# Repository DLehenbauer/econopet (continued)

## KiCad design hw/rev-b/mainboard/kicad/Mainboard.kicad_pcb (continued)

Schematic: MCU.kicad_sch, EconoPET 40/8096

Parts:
C3, C6, C90, C93, C94, C95, C96, C97, C98: 100n; C_0402_1005Metric; LCSC Part # C307331
C86, C87: 33p; C_0402_1005Metric; LCSC Part # C1562
C88, C91, C92: 2u2 6.3V; C_0402_1005Metric; LCSC Part # C12530
D11: LED_GRN; LED_0603_1608Metric; LCSC Part # C2986059
J23: MENU; PinHeader_1x02_P2.54mm_Vertical; MOUSER 649-1012937891002BLF
JP7: DVI_CEC; SolderJumper-2_P1.3mm_Open_RoundedPad1.0x1.5mm
R39: 10k; R_0402_1005Metric; LCSC Part # C25744
R40: 4k7; R_0402_1005Metric; LCSC Part # C25900
R41, R42, R43: 1k; R_0402_1005Metric; LCSC Part # C11702
R44, R45, R48, R49: 2k2; R_0402_1005Metric; LCSC Part # C25879
R46, R47: 27; R_0603_1608Metric; LCSC Part # C25190
SW4: TS-1088-AR02016; SW-SMD_L3.9-W3.0-P4.45; LCSC Part # C720477
SW5: MENU_BTN; APEM_MJTP1117; MOUSER 642-MJTP1117
U21: RP2040; LQFN-56_L7.0-W7.0-P0.4-EP; LCSC Part # C2040
Y1: 12 MHz; Crystal_SMD_3225-4Pin_3.2x2.5mm; LCSC Part # C9002

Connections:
+3V3: C92.1, C93.1, C94.1, C95.1, C96.1, C97.1, C98.1, R40.1, R44.1, R45.1, R48.1, R49.1, U21.1 (IOVDD), U21.10 (IOVDD), U21.22 (IOVDD), U21.33 (IOVDD), U21.42 (IOVDD), U21.43 (ADC_AVDD), U21.44 (VREG_IN), U21.48 (USB_VDD), U21.49 (IOVDD); also elsewhere on the board
/MAGIC/FPGA/CEC: JP7.1 (A), U21.36 (GPIO24); also elsewhere on the board
/MAGIC/FPGA/FPGA_CLK: U21.18 (GPIO15); also elsewhere on the board
/MAGIC/FPGA/I2C0_SCL: R49.2, U21.41 (GPIO29_ADC3); also elsewhere on the board
/MAGIC/FPGA/I2C0_SDA: R48.2, U21.40 (GPIO28_ADC2); also elsewhere on the board
/MAGIC/FPGA/I2C1_SCL: R45.2, U21.5 (GPIO3); also elsewhere on the board
/MAGIC/FPGA/I2C1_SDA: R44.2, U21.4 (GPIO2); also elsewhere on the board
/MAGIC/FPGA/SPI0_RX: U21.6 (GPIO4); also elsewhere on the board
/MAGIC/FPGA/SPI0_SCK: U21.8 (GPIO6); also elsewhere on the board
/MAGIC/FPGA/SPI0_TX: U21.9 (GPIO7); also elsewhere on the board
/MAGIC/FPGA/SPI0_~CS: U21.7 (GPIO5); also elsewhere on the board
/MAGIC/FPGA/SPI1_RX: U21.15 (GPIO12); also elsewhere on the board
/MAGIC/FPGA/SPI1_SCK: U21.17 (GPIO14); also elsewhere on the board
/MAGIC/FPGA/SPI1_TX: U21.14 (GPIO11); also elsewhere on the board
/MAGIC/FPGA/SPI1_~CS: U21.16 (GPIO13); also elsewhere on the board
/MAGIC/FPGA/SPI1_~READY: U21.13 (GPIO10); also elsewhere on the board
/MAGIC/FPGA/SWCLK: U21.24 (SWCLK); also elsewhere on the board
/MAGIC/FPGA/SWD: U21.25 (SWD); also elsewhere on the board
/MAGIC/FPGA/UART_RX: U21.3 (GPIO1); also elsewhere on the board
/MAGIC/FPGA/UART_TX: U21.2 (GPIO0); also elsewhere on the board
/MAGIC/FPGA/~CRESET: R39.2; also elsewhere on the board
/MAGIC/FPGA/~SPI_ENA: C6.1, R40.2, R41.2, U21.26 (RUN); also elsewhere on the board
/MAGIC/MCU/DVDD: C3.1, C90.1, C91.1, U21.23 (DVDD), U21.45 (VREG_VOUT), U21.50 (DVDD)
/MAGIC/MCU/DVI/CEC: JP7.2 (B); also elsewhere on the board
/MAGIC/MCU/DVI/DVI_CK+: U21.28 (GPIO17); also elsewhere on the board
/MAGIC/MCU/DVI/DVI_CK-: U21.27 (GPIO16); also elsewhere on the board
/MAGIC/MCU/DVI/DVI_D0+: U21.30 (GPIO19); also elsewhere on the board
/MAGIC/MCU/DVI/DVI_D0-: U21.29 (GPIO18); also elsewhere on the board
/MAGIC/MCU/DVI/DVI_D1+: U21.32 (GPIO21); also elsewhere on the board
/MAGIC/MCU/DVI/DVI_D1-: U21.31 (GPIO20); also elsewhere on the board
/MAGIC/MCU/DVI/DVI_D2+: U21.35 (GPIO23); also elsewhere on the board
/MAGIC/MCU/DVI/DVI_D2-: U21.34 (GPIO22); also elsewhere on the board
/MAGIC/MCU/Flash/SCK: U21.52 (QSPI_SCLK); also elsewhere on the board
/MAGIC/MCU/Flash/SD0: U21.53 (QSPI_SD0); also elsewhere on the board
/MAGIC/MCU/Flash/SD1: U21.55 (QSPI_SD1); also elsewhere on the board
/MAGIC/MCU/Flash/SD2: U21.54 (QSPI_SD2); also elsewhere on the board
/MAGIC/MCU/Flash/SD3: U21.51 (QSPI_SD3); also elsewhere on the board
/MAGIC/MCU/Flash/~CS: U21.56 (QSPI_SS); also elsewhere on the board
/MAGIC/MCU/GP25: R43.1, U21.37 (GPIO25)
/MAGIC/MCU/GP27: C88.1, J23.2, SW5.2, U21.39 (GPIO27_ADC1)
/MAGIC/MCU/MCU_USB_D+: R46.1, U21.47 (USB_DP)
/MAGIC/MCU/MCU_USB_D-: R47.1, U21.46 (USB_DM)
/MAGIC/MCU/MCU_~CRESET: R39.1, U21.38 (GPIO26_ADC0)
/MAGIC/MCU/SD_DETECT: U21.11 (GPIO8); also elsewhere on the board
/MAGIC/MCU/SD_~CS: U21.12 (GPIO9); also elsewhere on the board
/MAGIC/MCU/USB/USB_D+: R46.2; also elsewhere on the board
/MAGIC/MCU/USB/USB_D-: R47.2; also elsewhere on the board
/MAGIC/MCU/XIN: C86.2, U21.20 (XIN), Y1.1
/MAGIC/MCU/XOUT: R42.2, U21.21 (XOUT)
GND: C3.2, C6.2, C86.1, C87.1, C88.2, C90.2, C91.2, C92.2, C93.2, C94.2, C95.2, C96.2, C97.2, C98.2, D11.1 (K), J23.1, SW4.1, SW5.1, U21.19 (TESTEN), U21.57 (GND), Y1.2, Y1.4; also elsewhere on the board
unnamed: C87.2, R42.1, Y1.3
unnamed: D11.2 (A), R43.2
unnamed: R41.1, SW4.2

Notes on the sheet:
100n at RUN pin for EMI immunity. Avoids reset during CRT sync lock.
IO/USB/AVDD Decoupling
The MCU configures the FPGA using SPI0. Once the FPGA is configured, the MCU can communicate asynchronously with the system bus over SPI0 using the FPGA as a bridge. The MCU uses SPI0 to initialize SRAM with the PET ROM contents at POR. Afterwards, Core0 of the MCU uses SPI0 to read back video RAM 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
Menu/Reset Button
Oscillator Specs: C_{L}=20pF C_{0}=7pF DL=1-200μW (100uW typical) ESR=80Ω Load capacitor calculation: C = 2*C_{L} - 2*C_{stray} C_{L} = 20pf, C_{stray} = 2-5pF C = 30-36pF AMS1117-3.3 may require increasing PICO_XOSC_STARTUP_DELAY_MULTIPLIER to allow more time for 3V3 to stabilize. The TLV1117LV ap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
The T8/20Q144 requires SPI0_~{CS} to be pulsed low, even when using JTAG. To prevent contention on SPI0_~{CS}, we use ~{SPI_ENA} to reset the RP2040, which then detects that ~{CRESET} is being actively driven hi and skips JTAG configuration. POR Idle Programming ~SPI0_~{CS} float hi Pulse lo -> hi 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
MCU
MCU Status LED
On short press, MCU triggers a CPU reset. On long press, MCU enters menu.
DVDD Decoupling
10k resistor allows FPGA programmer to override ~{CRESET} during JTAG configuration.

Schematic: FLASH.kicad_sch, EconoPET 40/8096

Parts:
C1: 100n; C_0402_1005Metric; LCSC Part # C307331
R65: 1k; R_0402_1005Metric; LCSC Part # C11702
R66: 10k; R_0402_1005Metric; LCSC Part # C25744
SW6: TS-1088-AR02016; SW-SMD_L3.9-W3.0-P4.45; LCSC Part # C720477
U22: W25Q128JVS; SOIC-8_5.23x5.23mm_P1.27mm; LCSC Part # C97521

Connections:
+3V3: C1.1, R66.1, U22.8 (VCC); also elsewhere on the board
/MAGIC/MCU/Flash/SCK: U22.6 (CLK); also elsewhere on the board
/MAGIC/MCU/Flash/SD0: U22.5 (DI(IO0)); also elsewhere on the board
/MAGIC/MCU/Flash/SD1: U22.2 (DO(IO1)); also elsewhere on the board
/MAGIC/MCU/Flash/SD2: U22.3 (IO2); also elsewhere on the board
/MAGIC/MCU/Flash/SD3: U22.7 (IO3); also elsewhere on the board
/MAGIC/MCU/Flash/~CS: R65.2, R66.2, U22.1 (~CS); also elsewhere on the board
GND: C1.2, SW6.1, U22.4 (GND); also elsewhere on the board
unnamed: R65.1, SW6.2

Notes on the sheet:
16MiB Quad SPI flash memory for MCU. Holding BOOTSEL at power on puts the MCU into programming mode, allowing new firmware to be uploaded via USB for initial programming and recovery. (Typically, firmware updates happen via microSD instead.)
Flash

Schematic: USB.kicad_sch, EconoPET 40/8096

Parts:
C102: 47u 10V; C_1206_3216Metric; LCSC Part # C96123
C103: 1u; C_0402_1005Metric; LCSC Part # C52923
D12: SS54; D_SMA; LCSC Part # C22452
J26: USB1.1_HOST_TYPE_C; USB-C_SMD-TYPE-C-31-M-12; LCSC Part # C165948
R63, R64: 56k; R_0402_1005Metric; LCSC Part # C25796

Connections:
+5V: D12.2 (A); also elsewhere on the board
/MAGIC/MCU/USB/CC1: J26.A5 (CC1), R63.2
/MAGIC/MCU/USB/CC2: J26.B5 (CC2), R64.2
/MAGIC/MCU/USB/USB_D+: J26.A6 (D+), J26.B6 (D+); also elsewhere on the board
/MAGIC/MCU/USB/USB_D-: J26.A7 (D-), J26.B7 (D-); also elsewhere on the board
/MAGIC/MCU/USB/VBUS: C102.1, C103.1, D12.1 (K), J26.A4_B9 (VBUS), J26.A9_B4 (VBUS), R63.1, R64.1
GND: C102.2, C103.2, J26.A1_B12 (GND), J26.A12_B1 (GND), J26.S1 (SHIELD); also elsewhere on the board

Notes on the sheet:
USB
USB 1.1 Host over USB-C connector The 56k pullups on CC1 and CC2 identify the port as downstream facing, supplying 5V/900ma. The diode prevents connected devices from inadvertently backpowering the EconoPET. V_{F} < 0.5V should be within USB spec of 5V +/-10% (4.5V - 5.5V). The 47u capacitor helps 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

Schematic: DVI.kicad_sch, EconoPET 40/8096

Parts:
C99: 4u7 10V; C_0402_1005Metric; LCSC Part # C23733
J24: NOT_HDMI_A; HDMI_A_Molex_208658-1001_Horizontal; LCSC Part # C138388
R50, R51, R52: 2k2; R_0402_1005Metric; LCSC Part # C25879
R53, R54, R55, R56, R57, R58, R59, R60, R61: 270; R_0603_1608Metric; LCSC Part # C22966

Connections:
+3V3: R50.1; also elsewhere on the board
+5V: C99.1, J24.18 (+5V), R51.1, R52.1; also elsewhere on the board
/MAGIC/MCU/DVI/CEC: R50.2, R61.1; also elsewhere on the board
/MAGIC/MCU/DVI/DVI_CK+: R59.1; also elsewhere on the board
/MAGIC/MCU/DVI/DVI_CK-: R60.1; also elsewhere on the board
/MAGIC/MCU/DVI/DVI_D0+: R57.1; also elsewhere on the board
/MAGIC/MCU/DVI/DVI_D0-: R58.1; also elsewhere on the board
/MAGIC/MCU/DVI/DVI_D1+: R55.1; also elsewhere on the board
/MAGIC/MCU/DVI/DVI_D1-: R56.1; also elsewhere on the board
/MAGIC/MCU/DVI/DVI_D2+: R53.1; also elsewhere on the board
/MAGIC/MCU/DVI/DVI_D2-: R54.1; also elsewhere on the board
/MAGIC/MCU/DVI/HDMI_CEC: J24.13 (CEC), R61.2
/MAGIC/MCU/DVI/HDMI_CK+: J24.10 (CK+), R59.2
/MAGIC/MCU/DVI/HDMI_CK-: J24.12 (CK-), R60.2
/MAGIC/MCU/DVI/HDMI_D0+: J24.7 (D0+), R57.2
/MAGIC/MCU/DVI/HDMI_D0-: J24.9 (D0-), R58.2
/MAGIC/MCU/DVI/HDMI_D1+: J24.4 (D1+), R55.2
/MAGIC/MCU/DVI/HDMI_D1-: J24.6 (D1-), R56.2
/MAGIC/MCU/DVI/HDMI_D2+: J24.1 (D2+), R53.2
/MAGIC/MCU/DVI/HDMI_D2-: J24.3 (D2-), R54.2
GND: C99.2, J24.2 (D2S), J24.5 (D1S), J24.8 (D0S), J24.11 (CKS), J24.17 (GND), J24.SH; also elsewhere on the board
unnamed: J24.15 (SCL), R51.2
unnamed: J24.16 (SDA), R52.2

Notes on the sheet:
NOT
DVI TMDS protocol over an HDMI-compatible connector (not HDMI certified). See: https://github.com/Wren6991/PicoDVI
DVI VIDEO

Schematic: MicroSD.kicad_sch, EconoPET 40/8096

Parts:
C2: 100n; C_0402_1005Metric; LCSC Part # C307331
C101: 47u 10V; C_1206_3216Metric; LCSC Part # C96123
J25: MICRO_SD; TF-SMD_TF-PUSH; LCSC Part # C393941
R62: 10k; R_0402_1005Metric; LCSC Part # C25744
RN16: 10kx4; R_Array_Convex_4x0603; LCSC Part # C29718

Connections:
+3V3: C2.1, C101.1, J25.4 (VDD), R62.1, RN16.5 (R4.2), RN16.6 (R3.2), RN16.7 (R2.2), RN16.8 (R1.2); also elsewhere on the board
/MAGIC/FPGA/SPI1_RX: J25.7 (DAT0), RN16.3 (R3.1); also elsewhere on the board
/MAGIC/FPGA/SPI1_SCK: J25.5 (CLK); also elsewhere on the board
/MAGIC/FPGA/SPI1_TX: J25.3 (CMD), RN16.2 (R2.1); also elsewhere on the board
/MAGIC/MCU/SD_DETECT: J25.9 (DET); also elsewhere on the board
/MAGIC/MCU/SD_~CS: J25.2 (DAT3/CD), RN16.1 (R1.1); also elsewhere on the board
GND: C2.2, C101.2, J25.6 (VSS), J25.10 (SHIELD); also elsewhere on the board
unnamed: J25.8 (DAT1), RN16.4 (R4.1)
unnamed: J25.1 (DAT2), R62.2

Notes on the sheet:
47uF decoupling capacitor helps inrush current (although hot insertion is not recommended).
DAT[0] : (POCI) is open-drain output that requires pullup. DAT[2:1] : Unused inputs in SPI mode. Pullups recommended to avoid current draw due to metastablitiy. DAT[3] : (~{CS}) has built-in 22-50k pullup to ensure card is deselected by default. CMD : (PICO) input in SPI mode. CLK : (SCK) always an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
MicroSD

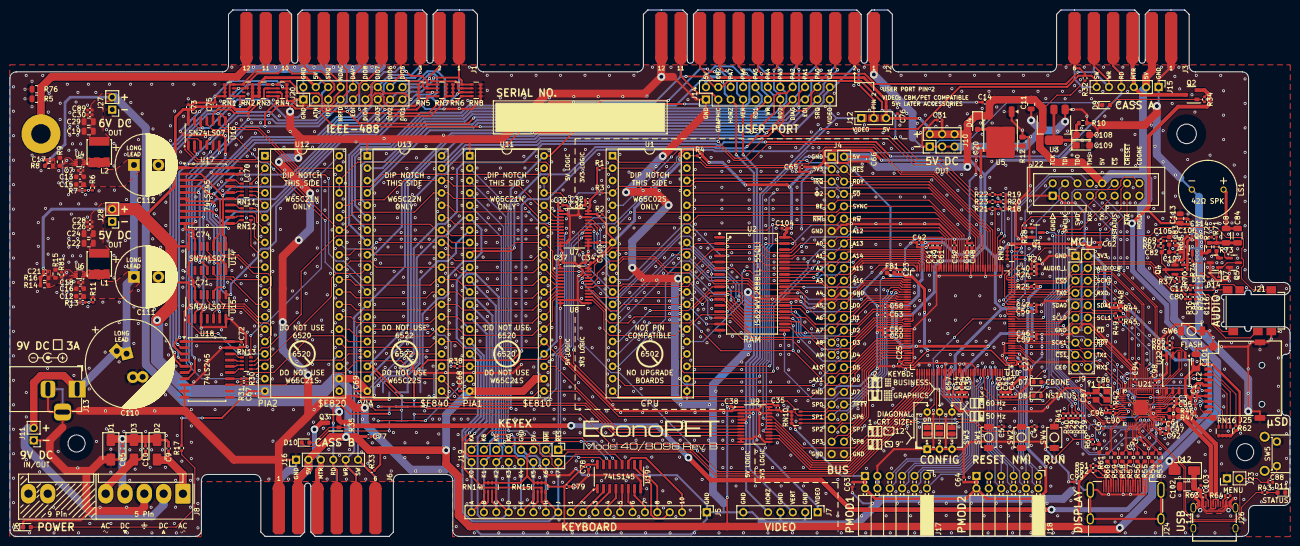
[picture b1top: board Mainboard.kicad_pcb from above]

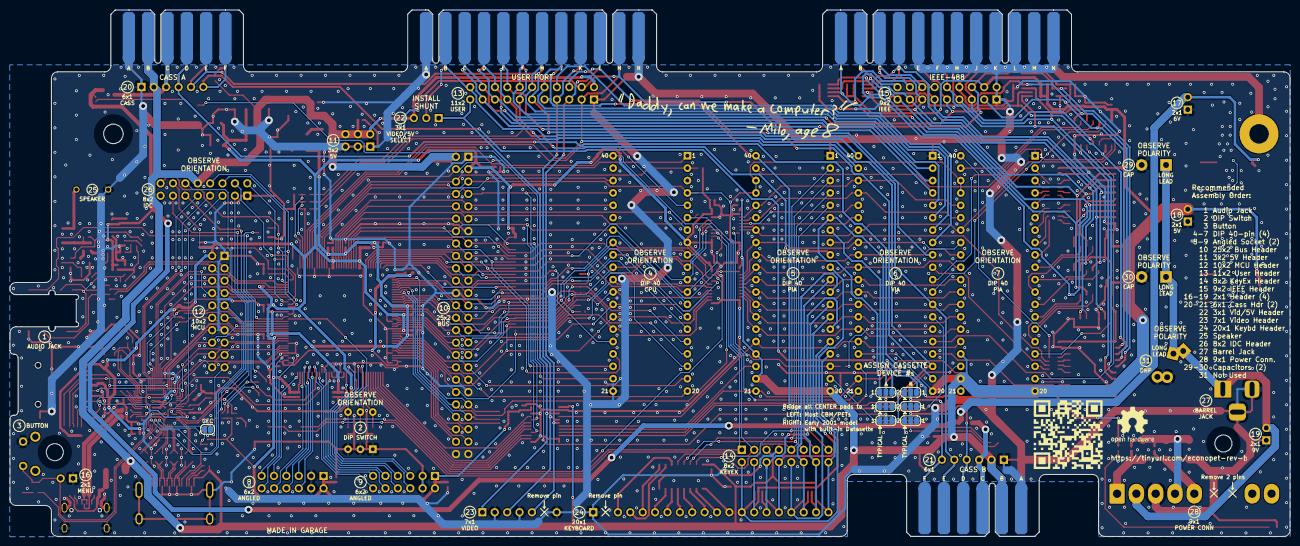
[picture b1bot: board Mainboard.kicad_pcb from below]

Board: 2 copper layers, 262.5 x 107.9 mm, 305 parts (10 on the bottom side), 325 nets.

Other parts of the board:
H2: MountingHole_Screw; MountingHole_4mm
H3, H4: MountingHole_Pillar; MountingHole_3.5mm
SYM1: SYM_Arrow_Small; Symbol_Barrel_Polarity
SYM2: SYM_Arrow_Small; EconoPET_Milo
SYM3: SYM_Arrow_Small; EconoPET_Model
SYM4: SYM_Arrow_Small; OSHW-Logo2_9.8x8mm_SilkScreen
SYM5: SYM_Arrow_Small; EconoPET_QR_Rev_B

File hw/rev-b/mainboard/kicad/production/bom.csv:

Designator,Footprint,Quantity,Value,LCSC Part #
"C1, C100, C104, C106, C107, C14, C18, C2, C25, C27, C28, C3, C33, C34, C35, C36, C37, C38, C40, C44, C45, C46, C47, C48, C49, C50, C51, C52, C53, C55, C57, C59, C6, C67, C68, C69, C7, C70, C71, C72, C73, C74, C78, C83, C89, C90, C93, C94, C95, C96, C97, C98",0402,52,100n,C307331
"C10, C116, C81, C85, C9",0402,5,22n,C1532
"C101, C102, C8, C84",1206,4,47u 10V,C96123
"C103, C114, C115, C20, C39, C41, C42, C43, C80",0402,9,1u,C52923
C105,0603,1,47n,C1622
"C108, C109",CP_EIA-3216-18_Kemet-A,2,10u 16V,C7171
"C11, C113, C19, C22, C24, C29",0805,6,22u,C45783
"C12, C13, C15, C16",0603,4,10u,C96446
"C17, C21, C86, C87",0402,4,33p,C1562
"C23, C26, C30, C31, C32, C62, C63, C64, C65, C66, C75, C76, C77, C79, C99",0402,15,4u7 10V,C23733
"C54, C56, C58, C60, C61",0402,5,10n,C15195
C82,0603,1,68n,C31658
"C88, C91, C92",0402,3,2u2 6.3V,C12530
"D1, D12, D2, D3",D_SMA,4,SS54,C22452
"D10, D6, D8, D9",0603,4,LED_RED,C2286
"D11, D7",0603,2,LED_GRN,C2986059
"D13, D14",D_SOD-323,2,1N4148WS,C2128
D4,D_SOD-123F,1,SM4007,C64898
FB1,0603,1,600 200ma,C1002
J24,HDMI_A_Molex_208658-1001_Horizontal,1,NOT_HDMI_A,C138388
J25,TF-SMD_TF-PUSH,1,MICRO_SD,C393941
J26,USB-C_SMD-TYPE-C-31-M-12,1,USB1.1_HOST_TYPE_C,C165948
"L1, L2",IND-SMD_L5.0-W5.0_FNR50XXS,2,1.8uH,C167956
Q1,SOT-23,1,MMBT3904,C20526
"Q2, Q3",SOT-23_L2.9-W1.3-P1.90-LS2.4-BR,2,AO3401A,C15127
"Q4, Q5, Q6",SOT-23,3,SS8050,C2150
Q7,SOT-23,1,SS8550,C8542
"R1, R13, R2, R3, R4, R40",0402,6,4k7,C25900
R10,0603,1,330,C23138
"R11, R37",0402,2,22k,C25768
"R12, R5",0805,2,120,C17437
"R14, R16",0603,2,330k,C23137
R15,0603,1,68k,C23231
"R17, R34, R35, R67, R69",0402,5,1k5,C25867
"R18, R19, R20, R25, R32, R33, R39, R62, R66, R70",0402,10,10k,C25744
"R21, R22, R23",0402,3,5k6,C25908
"R24, R28, R71",0402,3,100k,C25741
"R26, R36, R6, R75",0402,4,12k,C25752
"R27, R29, R38, R41, R42, R43, R65, R74",0402,8,1k,C11702
"R30, R31",0402,2,470,C25117
"R44, R45, R48, R49, R50, R51, R52, R7",0402,8,2k2,C25879
"R46, R47",0603,2,27,C25190
"R53, R54, R55, R56, R57, R58, R59, R60, R61",0603,9,270,C22966
"R63, R64",0402,2,56k,C25796
R68,0402,1,680,C25130
"R72, R73",0603,2,1,C22936
R76,0805,1,150,C17471
R8,0603,1,120k,C25808
R81,0402,1,33K,C25779
R9,0603,1,13k,C22797
"RN1, RN10, RN14, RN15, RN16, RN4, RN5, RN8, RN9",R_Array_Convex_4x0603,9,10kx4,C29718
"RN11, RN12, RN13",R_Array_Convex_4x0603,3,470x4,C25510
"RN2, RN3, RN6, RN7",R_Array_Convex_4x0603,4,4k7x4,C1980
"SW1, SW2, SW4, SW6",SW-SMD_L3.9-W3.0-P4.45,4,TS-1088-AR02016,C720477
U10,LQFP-144_20x20mm_P0.5mm,1,T20Q144C3,C3278392
"U14, U15, U16",SOIC-14_3.9x8.7mm_P1.27mm,3,SN74LS07,C513513
"U17, U18",SOIC-20W_7.5x12.8mm_P1.27mm,2,74LS245,C129580
U19,SOIC-16_3.9x9.9mm_P1.27mm,1,74LS145,C60829
U2,SOP-32_L20.7-W11.3-P1.27-LS14.1-BL,1,IS62WV1288BLL-55QLI,C1351025
U21,LQFN-56_L7.0-W7.0-P0.4-EP,1,RP2040,C2040
U22,SOIC-8_5.23x5.23mm_P1.27mm,1,W25Q128JVS,C97521
U3,SOT-223-3_TabPin2,1,AMS1117-3.3,C6186
"U4, U6",SOT-563,2,TPS564247DRLR,C5244316
U5,TO-252-2,1,LM317AG-TN3-R,C75510
"U7, U8, U9",TSSOP-24_4.4x7.8mm_P0.65mm,3,SN74LVC4245A,C7859
Y1,Crystal_SMD_3225-4Pin_3.2x2.5mm,1,12 MHz,C9002

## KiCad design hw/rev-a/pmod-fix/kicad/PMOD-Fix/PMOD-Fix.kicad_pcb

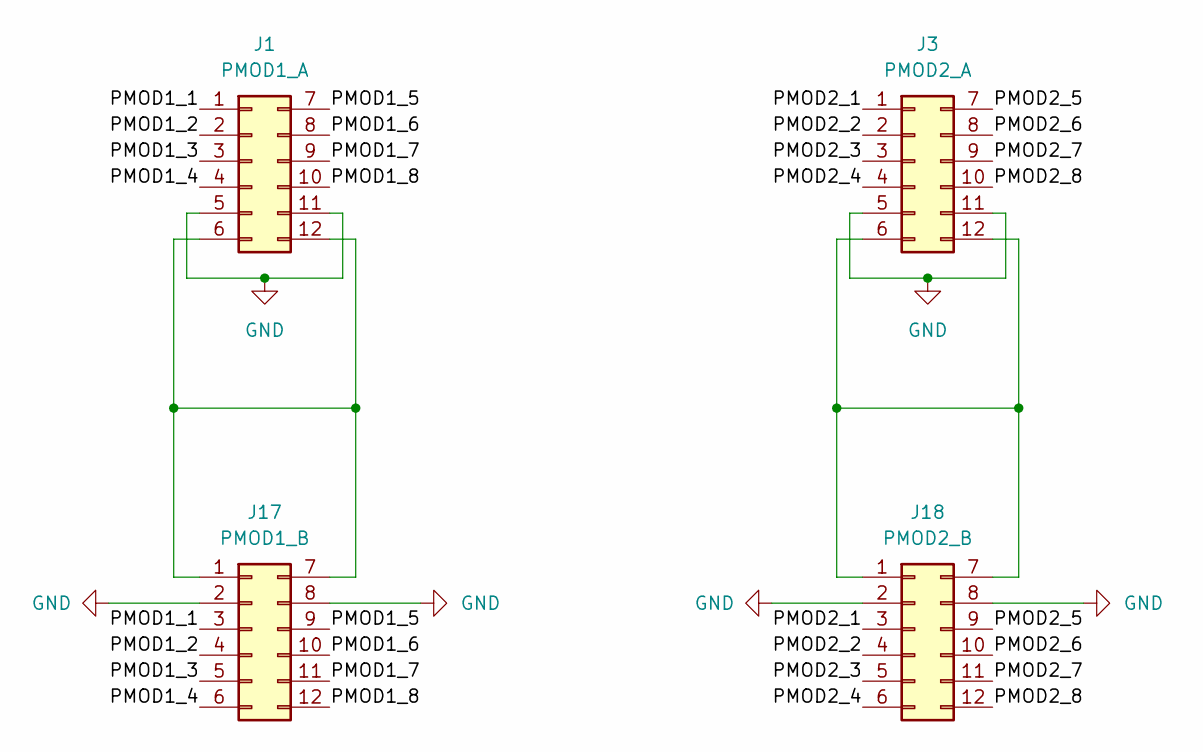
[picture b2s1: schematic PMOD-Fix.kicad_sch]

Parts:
J1: PMOD1_A; PMOD_Socket_2x06_P2.54mm_Horizontal; MOUSER 710-613012243121
J3: PMOD2_A; PMOD_Socket_2x06_P2.54mm_Horizontal; MOUSER 710-613012243121
J17: PMOD1_B; PMOD_Socket_2x06_P2.54mm_Horizontal; MOUSER 710-613012243121
J18: PMOD2_B; PMOD_Socket_2x06_P2.54mm_Horizontal; MOUSER 710-613012243121

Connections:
/PMOD1_1: J1.1, J17.3
/PMOD1_2: J1.2, J17.4
/PMOD1_3: J1.3, J17.5
/PMOD1_4: J1.4, J17.6
/PMOD1_5: J1.7, J17.9
/PMOD1_6: J1.8, J17.10
/PMOD1_7: J1.9, J17.11
/PMOD1_8: J1.10, J17.12
/PMOD2_1: J3.1, J18.3
/PMOD2_2: J3.2, J18.4
/PMOD2_3: J3.3, J18.5
/PMOD2_4: J3.4, J18.6
/PMOD2_5: J3.7, J18.9
/PMOD2_6: J3.8, J18.10
/PMOD2_7: J3.9, J18.11
/PMOD2_8: J3.10, J18.12
GND: J1.5, J1.11, J3.5, J3.11, J17.2, J17.8, J18.2, J18.8
unnamed: J1.6, J1.12, J17.1, J17.7
unnamed: J3.6, J3.12, J18.1, J18.7

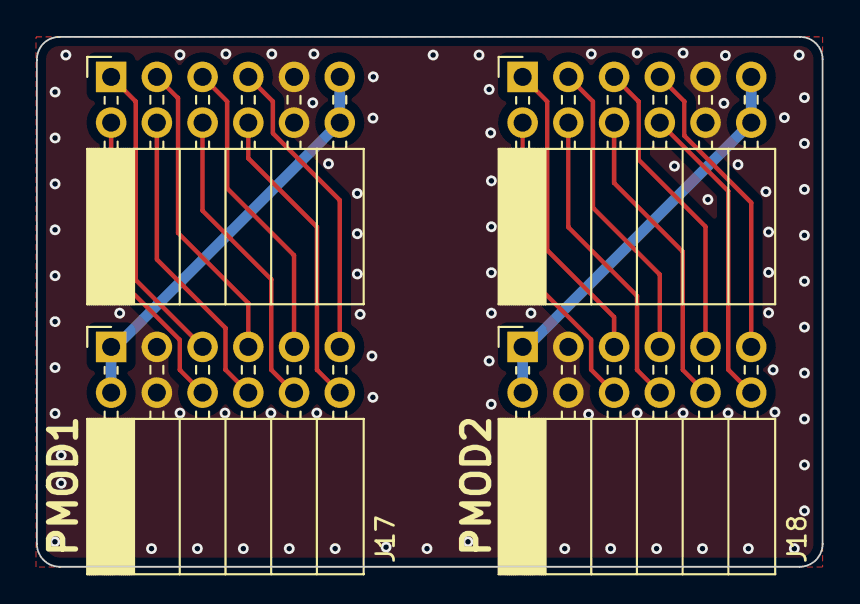
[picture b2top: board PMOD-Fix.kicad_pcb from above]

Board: 2 copper layers, 43.6 x 29.4 mm, 4 parts (0 on the bottom side), 19 nets.

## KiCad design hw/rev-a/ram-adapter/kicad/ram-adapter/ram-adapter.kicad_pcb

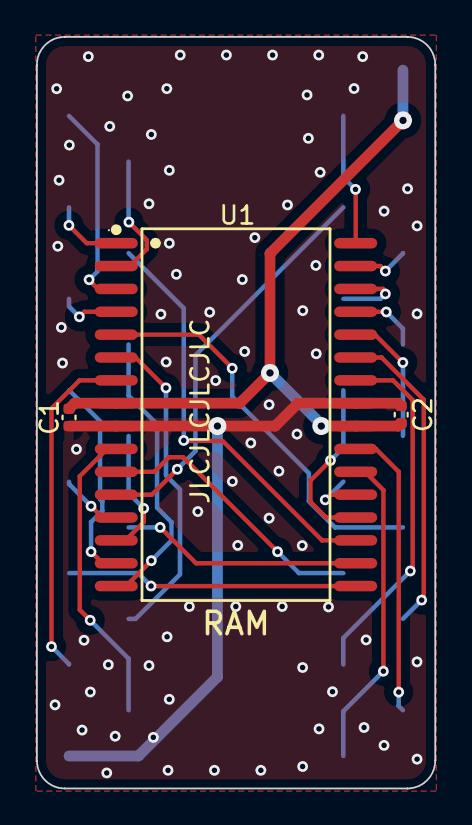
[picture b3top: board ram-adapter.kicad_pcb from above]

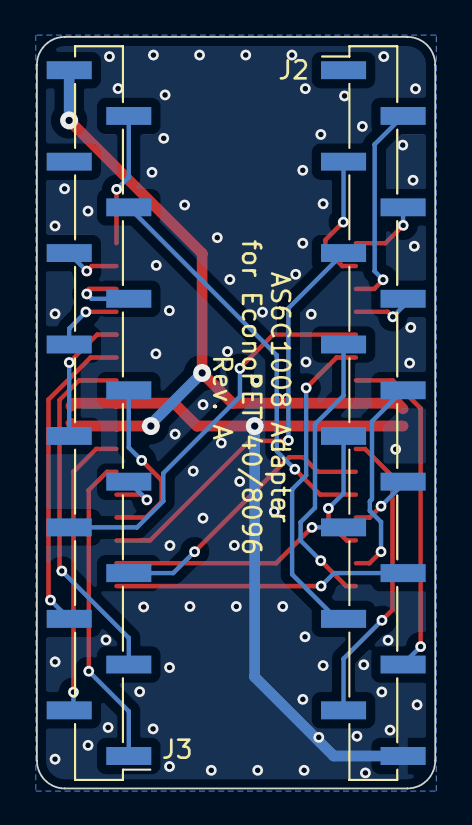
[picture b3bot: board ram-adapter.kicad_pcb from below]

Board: 2 copper layers, 22.1 x 41.8 mm, 5 parts (2 on the bottom side), 30 nets.

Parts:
C1, C2: 100n; C_0402_1005Metric
J2, J3: Conn_01x16_Male; PinHeader_1x16_P2.54mm_Vertical_SMD_Pin1Left
U1: IS61WV1288EEBLL; SOP-32_L20.7-W11.3-P1.27-LS14.1-BL

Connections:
/A0: J2.12, U1.17 (A8)
/A1: J2.11, U1.18 (A9)
/A2: J2.10, U1.13 (A4)
/A3: J2.9, U1.14 (A5)
/A4: J2.8, U1.15 (A6)
/A5: J2.7, U1.16 (A7)
/A6: J2.6, U1.4 (A3)
/A7: J2.5, U1.19 (A10)
/A8: J3.11, U1.30 (A14)
/A9: J3.10, U1.29 (A13)
/A10: J3.7, U1.21 (A12)
/A11: J3.9, U1.20 (A11)
/A12: J2.4, U1.1 (A0)
/A13: J3.12, U1.31 (A15)
/A14: J2.3, U1.2 (A1)
/A15: J3.15, U1.32 (A16)
/A16: J2.2, U1.3 (A2)
/D0: J2.13, U1.6 (IO0)
/D1: J2.14, U1.7 (IO1)
/D2: J2.15, U1.10 (IO2)
/D3: J3.1, U1.22 (IO4)
/D4: J3.2, U1.23 (IO5)
/D5: J3.3, U1.26 (IO6)
/D6: J3.4, U1.27 (IO7)
/D7: J3.5, U1.11 (IO3)
/~CE: J3.6, U1.5 (CE#)
/~OE: J3.8, U1.28 (OE#)
/~WE: J3.13, U1.12 (WE#)
GND: C1.2, C2.2, J2.16, U1.9 (GND), U1.25 (GND)
VCC: C1.1, C2.1, J3.16, U1.8 (VDD), U1.24 (VDD)

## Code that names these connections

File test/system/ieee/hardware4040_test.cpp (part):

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    EXPECT_FALSE(out.ndac);
}

// Native ATNIRQ reads $0287 to clear PA7, while $0285 is its flags mirror.
TEST_F(Hardware4040Test, RiotAtnEdgeLatchesWhileDisabledAndClearsOnFlagRead) {
    store(EdgePositiveDisabled, 0);
    run();
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    EXPECT_FALSE(machine.edge_pending[0]);
}

// Output-configured PA7 transitions also enter the edge detector.
TEST_F(Hardware4040Test, RiotPa7EdgeObservesOutputLatchAndDdr) {
    store(EdgePositiveEnabled, 0);
    store(ControlPort, 0x80);
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// Schematic 320806's discrete gates override software during ATN acknowledgement.
TEST_F(Hardware4040Test, AtnaRfdoDacoResolveEveryHandshakeCombination) {
    for (unsigned bits = 0; bits < 16; ++bits) {
        const bool atn = bits & 8, atna = bits & 1;
        const bool daco = bits & 2, rfdo = bits & 4;
        machine.ports[1][1] = 0xff;
        machine.ports[1][0] = bits & 7;
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    }
}

// Flags reads acknowledge PA7 only. Timer reads acknowledge timer and select IRQ.
TEST_F(Hardware4040Test, RiotTimerAndEdgeAcknowledgementsAreIndependent) {
    store(EdgePositiveEnabled, 0);
    store(0x029f, 0);
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    EXPECT_NE(machine.pins & M6502_IRQ, 0u);
}

// Reload discards the old timer event but preserves PA7, and expiry can occur again.
TEST_F(Hardware4040Test, TimerReloadRearmsAfterUnderflowWithoutAcknowledgingEdge) {
    for (const auto base : RiotBases) {
        program.clear();
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        resume(TimerDivisors[3]);
        EXPECT_TRUE(machine.timers[riot].pending);
        EXPECT_TRUE(machine.timers[riot].expired);
        // A flag read clears only PA7. Repeated reads must not restart the timer.
        next([&] { sample(base + 5, 0); });
        EXPECT_EQ(machine.shared[0x800], 0xc0);
        EXPECT_FALSE(machine.edge_pending[riot]);
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    }
}

// Changing RIOT0 PB's DIO contribution can cause a PA7 edge even without external activity.
TEST_F(Hardware4040Test, DdrAndDataOutputFeedbackBothReachRiotZeroEdgeDetector) {
    store(0x0204, 0);
    store(OutputPort, 0x7f);
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            rom4040_input(&machine, peer);
            resume(100);
            const bool atna = output & 1, daco = output & 2, rfdo = output & 4;
            const bool nrfd = (peer.atn != atna) && rfdo;
            const bool ndac = (peer.atn || atna) && !daco;
            const uint8_t pa = output | ((!peer.atn) ? 0x80 : 0)
                | ((peer.dav && (output & 16)) ? 0x40 : 0)
                | ((peer.eoi && (output & 8)) ? 0x20 : 0);
            const uint8_t pb = ((peer.nrfd && nrfd) ? 0x80 : 0)
                | ((peer.ndac && ndac) ? 0x40 : 0);
            ASSERT_EQ(machine.shared[0x800], pa) << output << " " << input;
            ASSERT_EQ(machine.shared[0x801], pb) << output << " " << input;
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    }
}

// PA7 senses both polarities even while masked, across every edge-control mirror.
TEST_F(Hardware4040Test, EveryEdgeControlMirrorPolarityMaskAndHeldLevel) {
    for (const auto base : RiotBases) {
        for (unsigned reg = 4; reg < 16; ++reg) {
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TEST_F(Hardware4040Test, FifoReceiveAllBytesAndMetadataHoldUntilCompleteHandshake) {
    for (unsigned value = 0; value < 256; ++value) {
        for (unsigned flags = 0; flags < 4; ++flags) {
            const bool atn = flags & 1, eoi = flags & 2;
            program.clear();
            store(ControlDdr, 0x1f);
            // Initially hold NRFD low, NDAC low.
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TEST_F(Hardware4040Test, FifoTransmitAllBytesEoiAndTerminationModesDoNotSpeculateGet) {
    for (unsigned value = 0; value < 256; ++value) {
        for (unsigned flags = 0; flags < 4; ++flags) {
            const bool eoi = flags & 1, get = flags & 2;
            program.clear();
            store(OutputDdr, 0xff);
            store(OutputPort, static_cast<uint8_t>(~value));
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
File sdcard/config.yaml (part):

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          # the beam was outside the visible region to avoid "sparkle" artifacts.
          #
          # On later CRTC models, the polling is unnecessary and results in extremely slow
          # text output due to VIA/PB5 being connected to VERT instead of VIDEO_ON/SYNC.
          #
          # The patch below elides the polling loop.
          - action: "copy"
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          # identical except that:
          #
          #   - Starts up in lower case ($e220)
          #   - Polling VIA/PB5 (VIDEO_ON/SYNC) has been removed.
          #   - Minor rearrangements in the $e699-e768 range to make room for the business
          #     keyboard keyscan routine.  Noteably:
          #     - LDTB2 has moved from $e748 to $e74b
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      # outside the visible region to avoid "sparkle" artifacts.
      #
      # On later CRTC models, the polling is unnecessary and results in extremely slow
      # text output due to VIA/PB5 being connected to VERT instead of VIDEO_ON/SYNC.
      #
      # The patch below elides the polling loop.
      - action: "copy"
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      - if: "graphics"
        then:
          # All SuperPETs had a business keyboard. This patch replaces the four
          # 81-byte keyboard translation tables with graphics-keyboard mappings.
          # Default character mode unshifted.
          - action: "patch"
            address: 0xdf40
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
